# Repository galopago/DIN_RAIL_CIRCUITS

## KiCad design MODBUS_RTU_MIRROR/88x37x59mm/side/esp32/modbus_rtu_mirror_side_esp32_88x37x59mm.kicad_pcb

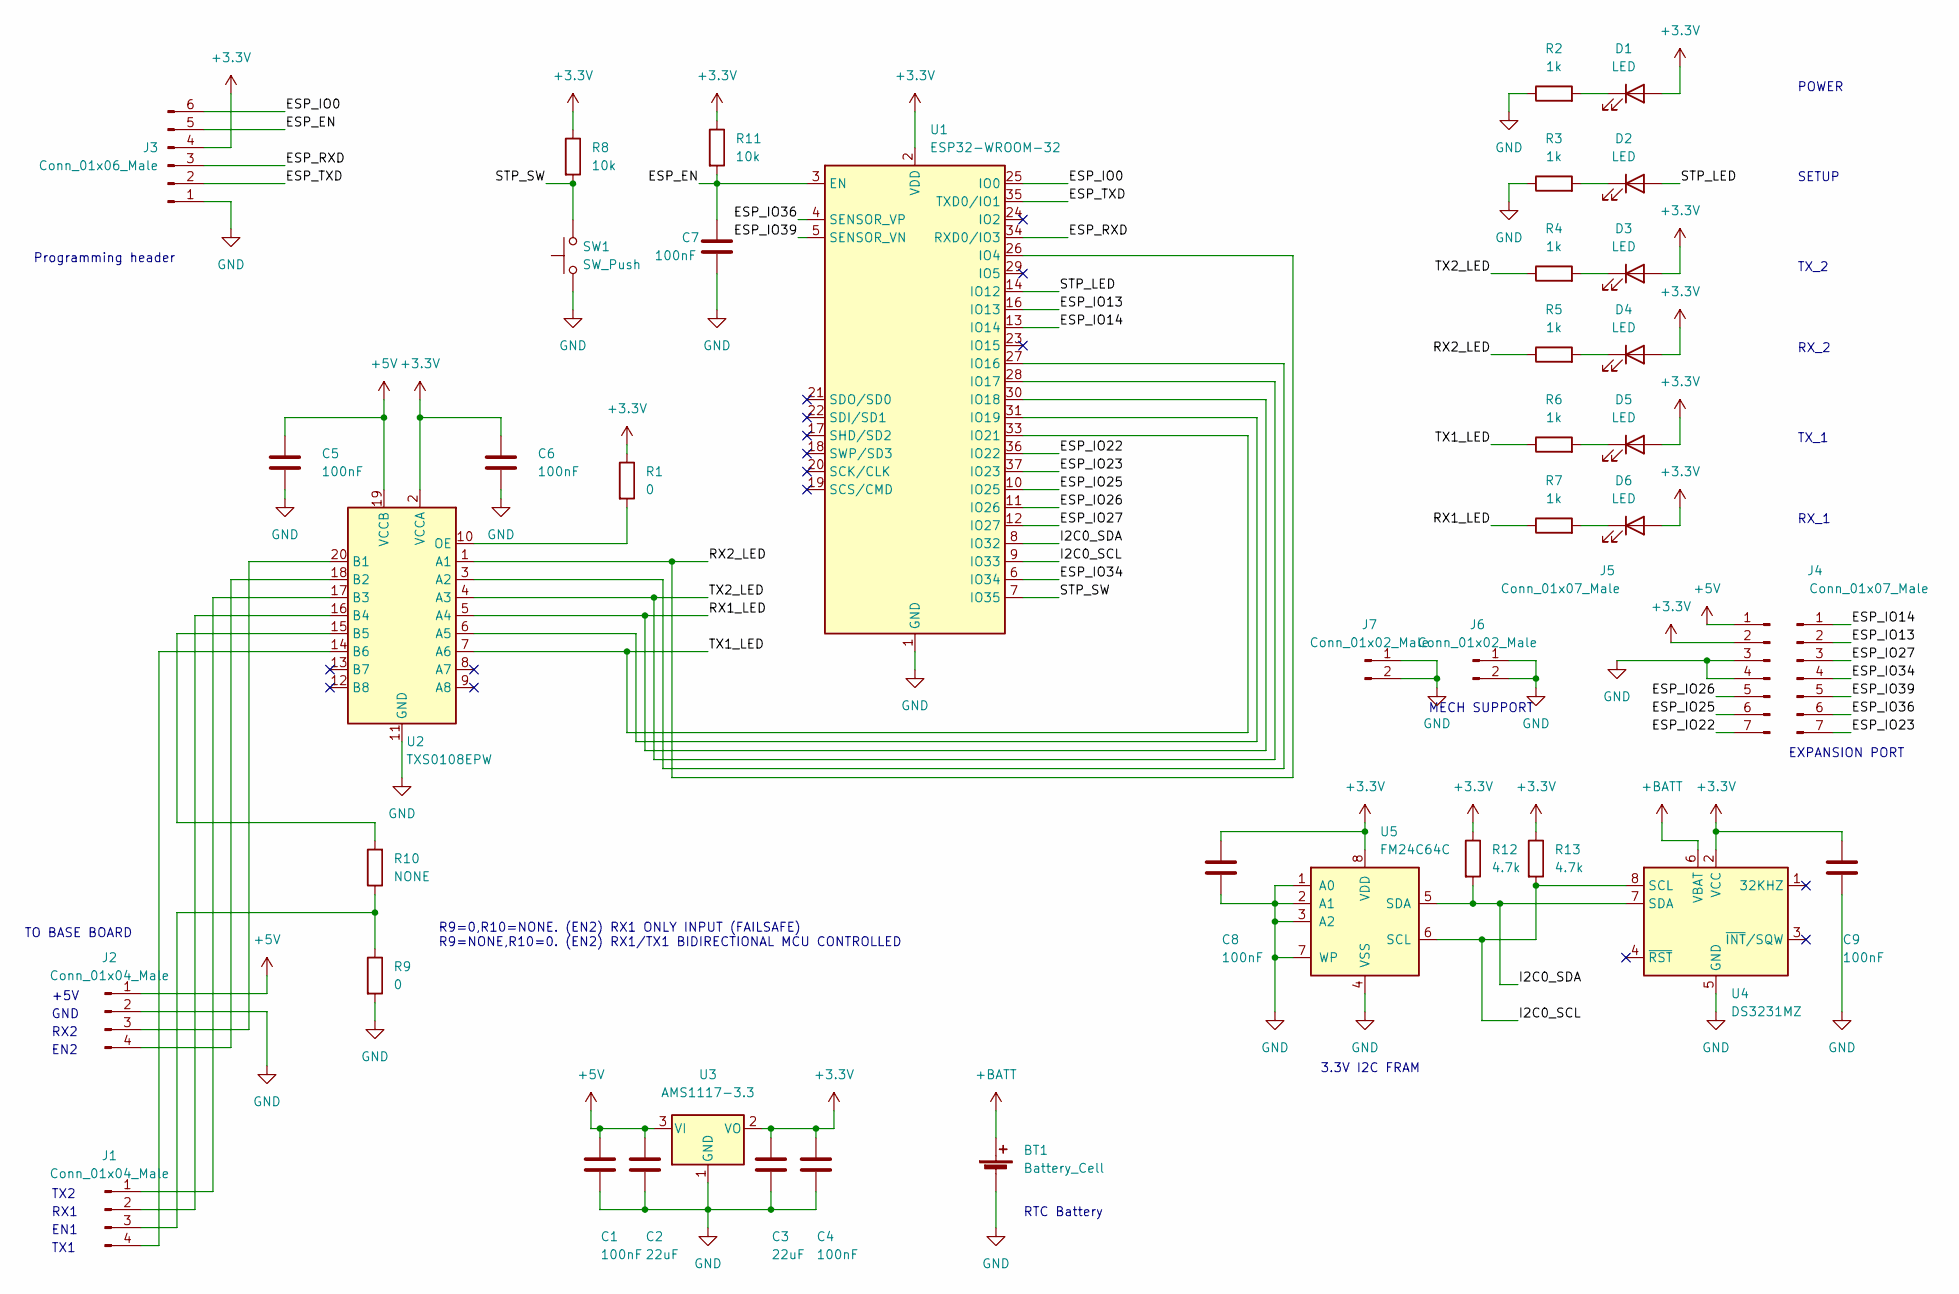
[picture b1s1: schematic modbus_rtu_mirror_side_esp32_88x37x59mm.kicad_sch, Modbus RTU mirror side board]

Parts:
BT1: Battery_Cell; CR2032_Vertical_CircularHoles
C1, C4, C5, C6, C7, C8, C9: 100nF; C_0805_2012Metric_Pad1.18x1.45mm_HandSolder
C2, C3: 22uF; C_0805_2012Metric_Pad1.18x1.45mm_HandSolder
D1, D2, D3, D4, D5, D6: LED; LED_D3.0mm_4.5x9.5mm
J1, J2: Conn_01x04_Male; PinHeader_1x04_P2.54mm_Vertical
J3: Conn_01x06_Male; PinHeader_1x06_P2.54mm_Vertical
J4, J5: Conn_01x07_Male; PinHeader_1x07_P1.00mm_Vertical
J6, J7: Conn_01x02_Male; PinHeader_1x02_P1.00mm_Vertical
R1, R9: 0; R_0805_2012Metric_Pad1.20x1.40mm_HandSolder
R2, R3, R4, R5, R6, R7: 1k; R_0805_2012Metric_Pad1.20x1.40mm_HandSolder
R8, R11: 10k; R_0805_2012Metric_Pad1.20x1.40mm_HandSolder
R10: NONE; R_0805_2012Metric_Pad1.20x1.40mm_HandSolder
R12, R13: 4.7k; R_0805_2012Metric_Pad1.20x1.40mm_HandSolder
SW1: SW_Push; SW_Tactile_SPST_Angled_PTS645Vx31-2LFS
U1: ESP32-WROOM-32
U2: TXS0108EPW; TSSOP-20_4.4x6.5mm_P0.65mm
U3: AMS1117-3.3; SOT-223-3_TabPin2
U4: DS3231MZ; SOIC-8_3.9x4.9mm_P1.27mm
U5: FM24C64C; SOIC-8_3.9x4.9mm_P1.27mm

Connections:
+3.3V: C3.1, C4.1, C6.1, C8.1, C9.1, D1.2 (A), D3.2 (A), D4.2 (A), D5.2 (A), D6.2 (A), J3.4, J5.2, R1.1, R8.1, R11.1, R12.1, R13.1, U1.2 (VDD), U2.2 (VCCA), U3.2 (VO), U4.2 (VCC), U5.8 (VDD)
+5V: C1.1, C2.1, C5.1, J2.1, J5.1, U2.19 (VCCB), U3.3 (VI)
+BATT: BT1.1 (+), U4.6 (VBAT)
/ESP_EN: C7.1, J3.5, R11.2, U1.3 (EN)
/ESP_IO0: J3.6, U1.25 (IO0)
/ESP_IO13: J4.2, U1.16 (IO13)
/ESP_IO14: J4.1, U1.13 (IO14)
/ESP_IO22: J5.7, U1.36 (IO22)
/ESP_IO23: J4.7, U1.37 (IO23)
/ESP_IO25: J5.6, U1.10 (IO25)
/ESP_IO26: J5.5, U1.11 (IO26)
/ESP_IO27: J4.3, U1.12 (IO27)
/ESP_IO34: J4.4, U1.6 (IO34)
/ESP_IO36: J4.6, U1.4 (SENSOR_VP)
/ESP_IO39: J4.5, U1.5 (SENSOR_VN)
/ESP_RXD: J3.3, U1.34 (RXD0/IO3)
/ESP_TXD: J3.2, U1.35 (TXD0/IO1)
/I2C0_SCL: R13.2, U1.9 (IO33), U4.8 (SCL), U5.6 (SCL)
/I2C0_SDA: R12.2, U1.8 (IO32), U4.7 (SDA), U5.5 (SDA)
/RX1_LED: R7.1, U1.30 (IO18), U2.5 (A4)
/RX2_LED: R5.1, U1.26 (IO4), U2.1 (A1)
/STP_LED: D2.2 (A), U1.14 (IO12)
/STP_SW: R8.2, SW1.1, U1.7 (IO35)
/TX1_LED: R6.1, U1.33 (IO21), U2.7 (A6)
/TX2_LED: R4.1, U1.28 (IO17), U2.4 (A3)
GND: BT1.2 (-), C1.2, C2.2, C3.2, C4.2, C5.2, C6.2, C7.2, C8.2, C9.2, J2.2, J3.1, J5.3, J5.4, J6.1, J6.2, J7.1, J7.2, R2.1, R3.1, R9.2, SW1.2, U1.1 (GND), U1.15 (GND), U1.38 (GND), U1.39 (GND), U2.11 (GND), U3.1 (GND), U4.5 (GND), U5.1 (A0), U5.2 (A1), U5.3 (A2), U5.4 (VSS), U5.7 (WP)
unnamed: D1.1 (K), R2.2
unnamed: D2.1 (K), R3.2
unnamed: D3.1 (K), R4.2
unnamed: D4.1 (K), R5.2
unnamed: D5.1 (K), R6.2
unnamed: D6.1 (K), R7.2
unnamed: J1.1, U2.17 (B3)
unnamed: J1.2, U2.16 (B4)
unnamed: J1.3, R9.1, R10.1
unnamed: J1.4, U2.14 (B6)
unnamed: J2.3, U2.20 (B1)
unnamed: J2.4, U2.18 (B2)
unnamed: R1.2, U2.10 (OE)
unnamed: R10.2, U2.15 (B5)
unnamed: U1.27 (IO16), U2.3 (A2)
unnamed: U1.31 (IO19), U2.6 (A5)

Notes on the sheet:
EXPANSION PORT
TO BASE BOARD
RX1
TX_2
EN2
RX2
MECH SUPPORT
RTC Battery
EN1
R9=0,R10=NONE. (EN2) RX1 ONLY INPUT (FAILSAFE) R9=NONE,R10=0. (EN2) RX1/TX1 BIDIRECTIONAL MCU CONTROLLED
TX2
GND
SETUP
Programming header
+5V
3.3V I2C FRAM
RX_1
TX_1
TX1
POWER
RX_2

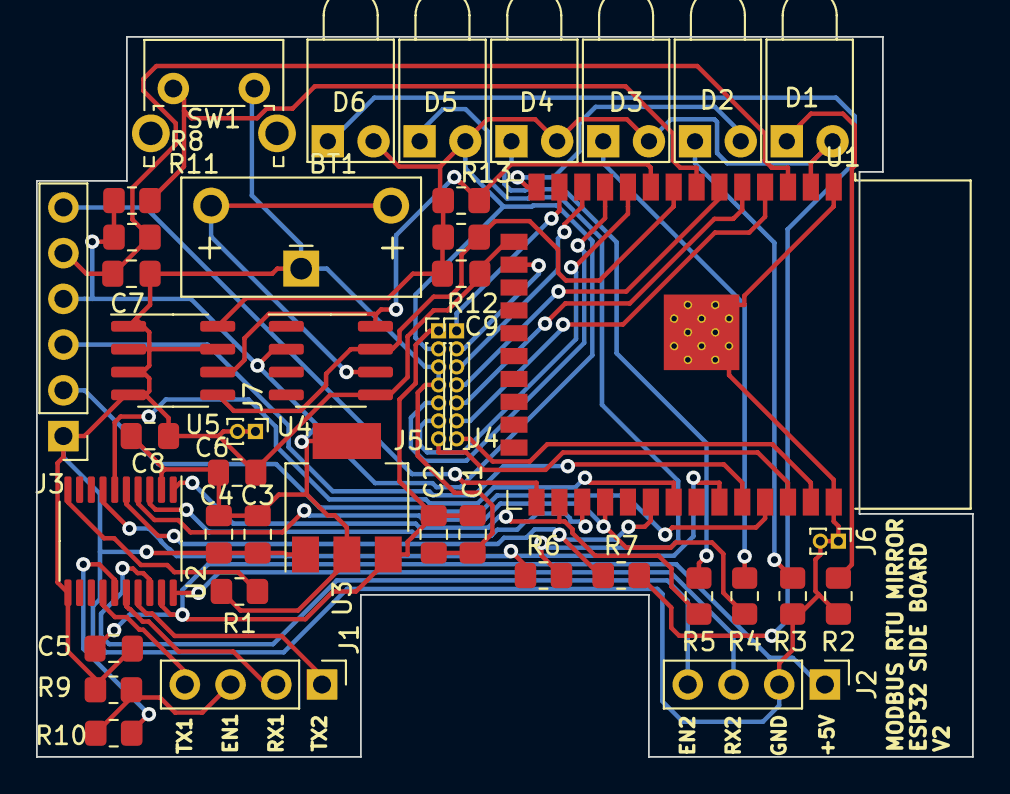
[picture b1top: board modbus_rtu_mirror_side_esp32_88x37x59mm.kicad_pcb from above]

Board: 2 copper layers, 52.0 x 40.0 mm, 42 parts (0 on the bottom side), 42 nets.

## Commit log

2025-02-18 added mech support pins for expansion board
